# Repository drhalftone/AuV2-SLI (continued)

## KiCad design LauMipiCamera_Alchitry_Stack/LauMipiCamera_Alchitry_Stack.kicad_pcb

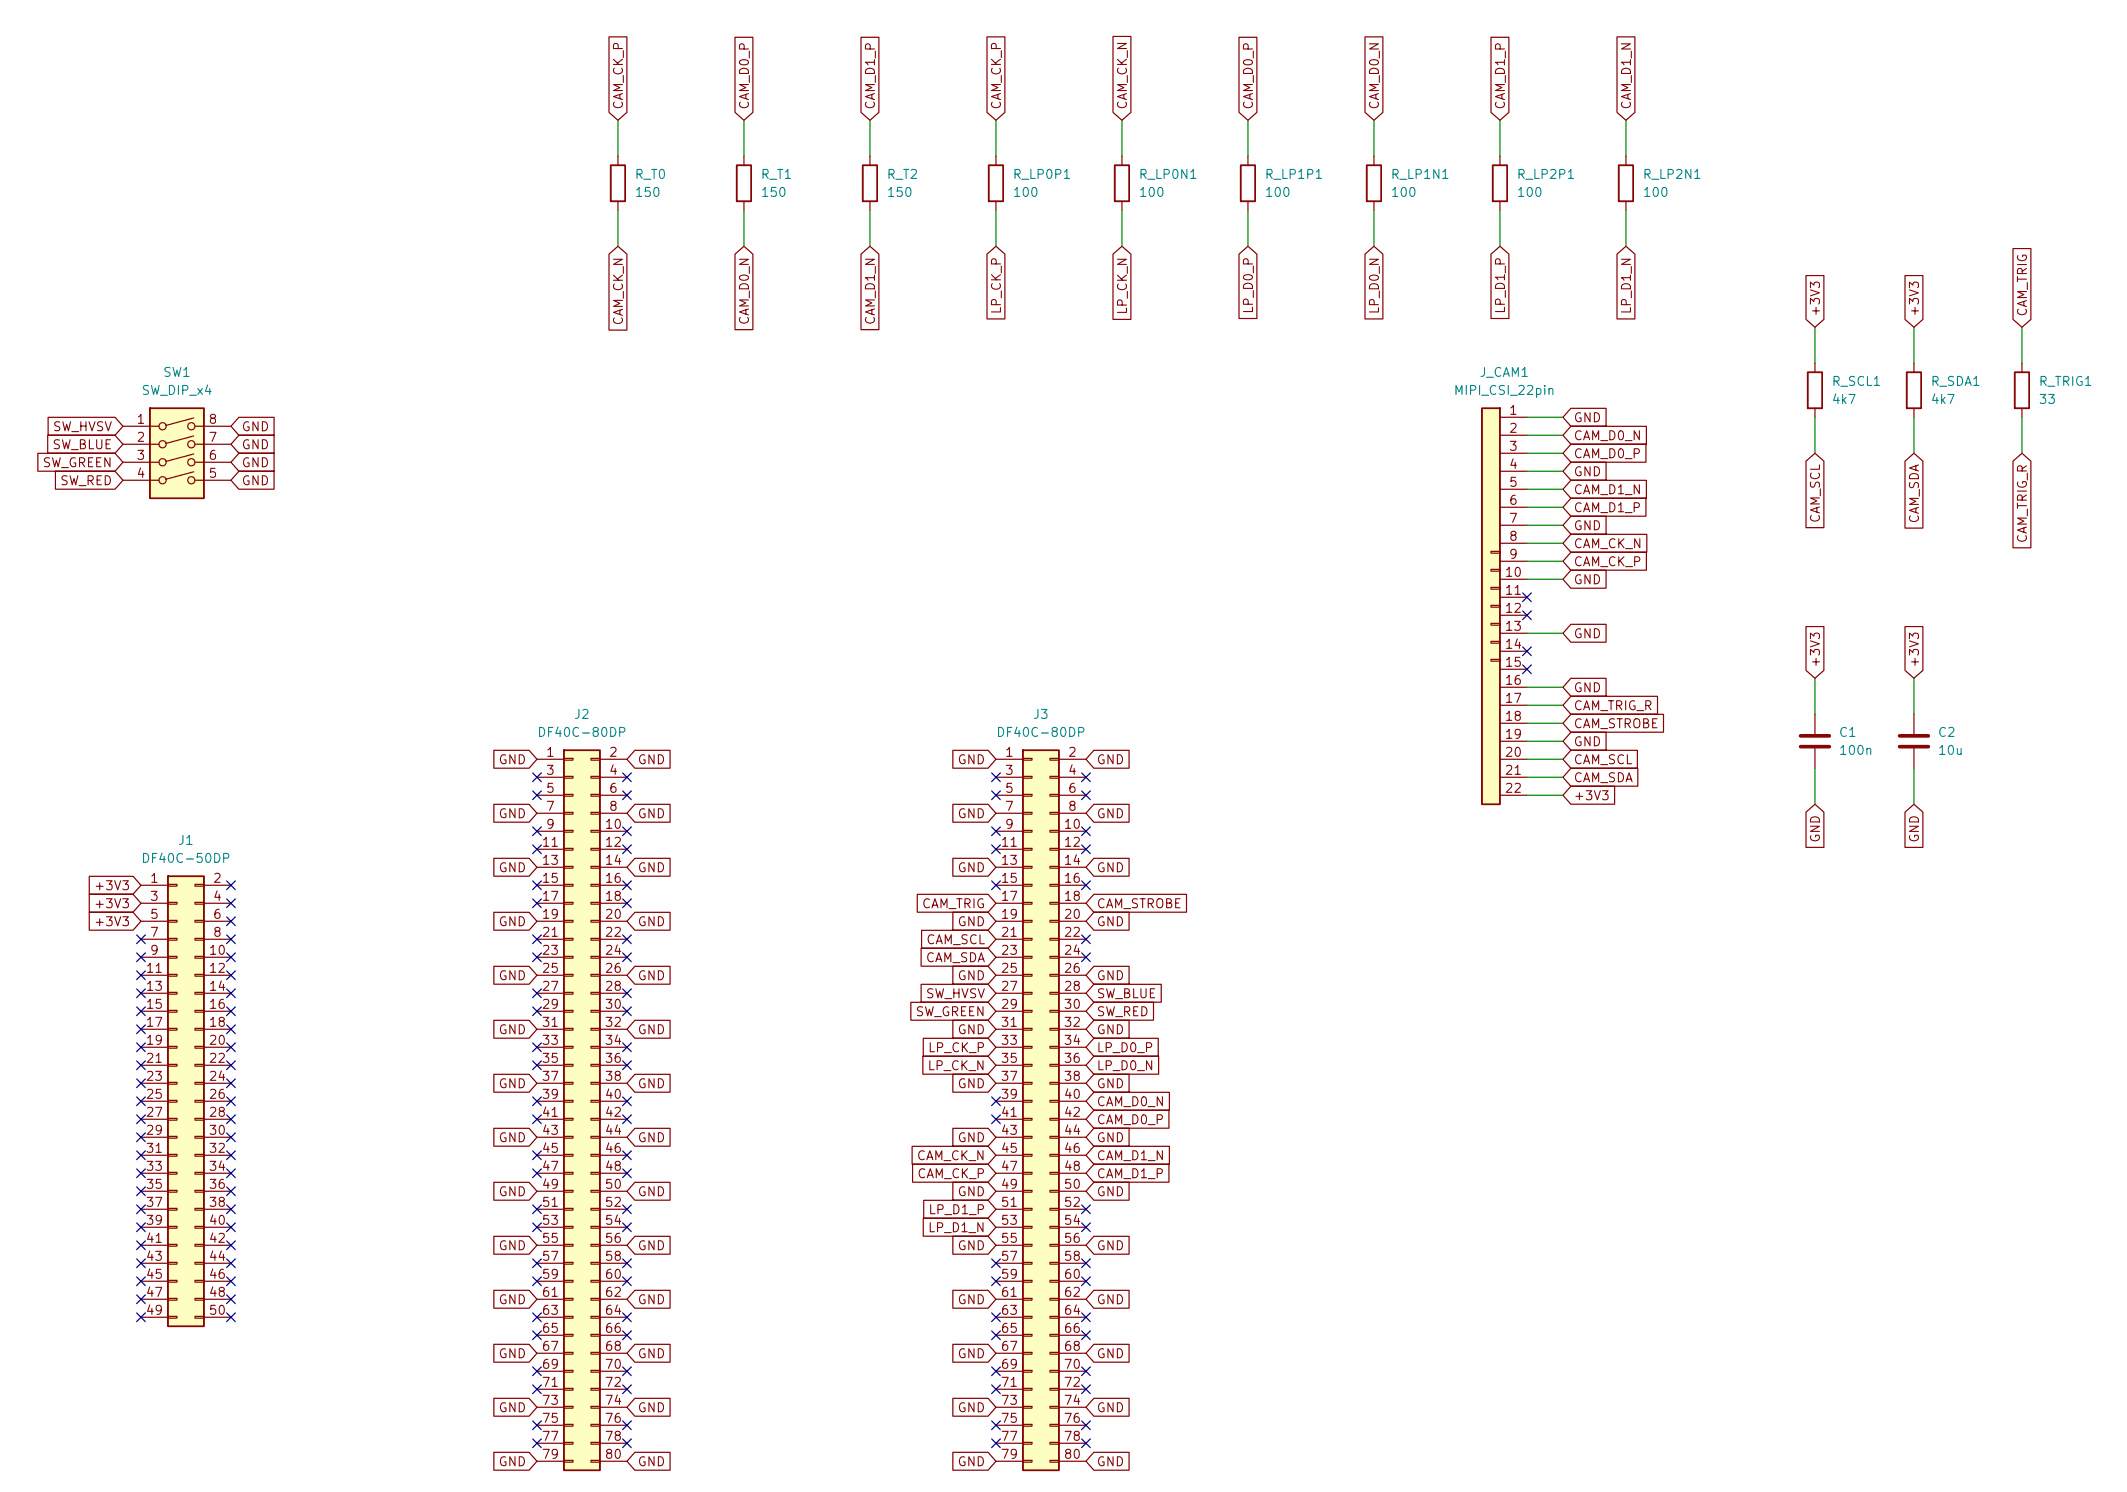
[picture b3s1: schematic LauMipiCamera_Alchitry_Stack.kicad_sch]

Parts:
C1: 100n; C_0805_2012Metric
C2: 10u; C_0805_2012Metric
J1: DF40C-50DP; Hirose_DF40C-50DP-0.4V_2x25-1MP_P0.4mm
J2, J3: DF40C-80DP; Hirose_DF40C-80DP-0.4V_2x40-1MP_P0.4mm
J_CAM1: MIPI_CSI_22pin; Hirose_FH12-22S-0.5SH_1x22-1MP_P0.50mm_Horizontal
R_LP0N1, R_LP0P1, R_LP1N1, R_LP1P1, R_LP2N1, R_LP2P1: 100; R_0402_1005Metric
R_SCL1: 4k7; R_0402_1005Metric
R_SDA1: 4k7; R_0402_1005Metric
R_T0, R_T1, R_T2: 150; R_0402_1005Metric
R_TRIG1: 33; R_0402_1005Metric
SW1: SW_DIP_x4; SW_DIP_SPSTx04_Slide_6.7x11.72mm_W8.61mm_P2.54mm_LowProfile

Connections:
+3V3: C1.1, C2.1, J1.1, J1.3, J1.5, J_CAM1.22, R_SCL1.1, R_SDA1.1
CAM_CK_N: J3.45, J_CAM1.8, R_LP0N1.1, R_T0.2
CAM_CK_P: J3.47, J_CAM1.9, R_LP0P1.1, R_T0.1
CAM_D0_N: J3.40, J_CAM1.2, R_LP1N1.1, R_T1.2
CAM_D0_P: J3.42, J_CAM1.3, R_LP1P1.1, R_T1.1
CAM_D1_N: J3.46, J_CAM1.5, R_LP2N1.1, R_T2.2
CAM_D1_P: J3.48, J_CAM1.6, R_LP2P1.1, R_T2.1
CAM_SCL: J3.21, J_CAM1.20, R_SCL1.2
CAM_SDA: J3.23, J_CAM1.21, R_SDA1.2
CAM_STROBE: J3.18, J_CAM1.18
CAM_TRIG: J3.17, R_TRIG1.1
CAM_TRIG_R: J_CAM1.17, R_TRIG1.2
GND: C1.2, C2.2, J2.1, J2.2, J2.7, J2.8, J2.13, J2.14, J2.19, J2.20, J2.25, J2.26, J2.31, J2.32, J2.37, J2.38, J2.43, J2.44, J2.49, J2.50, J2.55, J2.56, J2.61, J2.62, J2.67, J2.68, J2.73, J2.74, J2.79, J2.80, J3.1, J3.2, J3.7, J3.8, J3.13, J3.14, J3.19, J3.20, J3.25, J3.26, J3.31, J3.32, J3.37, J3.38, J3.43, J3.44, J3.49, J3.50, J3.55, J3.56, J3.61, J3.62, J3.67, J3.68, J3.73, J3.74, J3.79, J3.80, J_CAM1.1, J_CAM1.4, J_CAM1.7, J_CAM1.10, J_CAM1.13, J_CAM1.16, J_CAM1.19, SW1.5, SW1.6, SW1.7, SW1.8
LP_CK_N: J3.35, R_LP0N1.2
LP_CK_P: J3.33, R_LP0P1.2
LP_D0_N: J3.36, R_LP1N1.2
LP_D0_P: J3.34, R_LP1P1.2
LP_D1_N: J3.53, R_LP2N1.2
LP_D1_P: J3.51, R_LP2P1.2
SW_BLUE: J3.28, SW1.2
SW_GREEN: J3.29, SW1.3
SW_HVSV: J3.27, SW1.1
SW_RED: J3.30, SW1.4

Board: 4 copper layers, 19 parts (3 on the bottom side), 23 nets, no tracks yet.

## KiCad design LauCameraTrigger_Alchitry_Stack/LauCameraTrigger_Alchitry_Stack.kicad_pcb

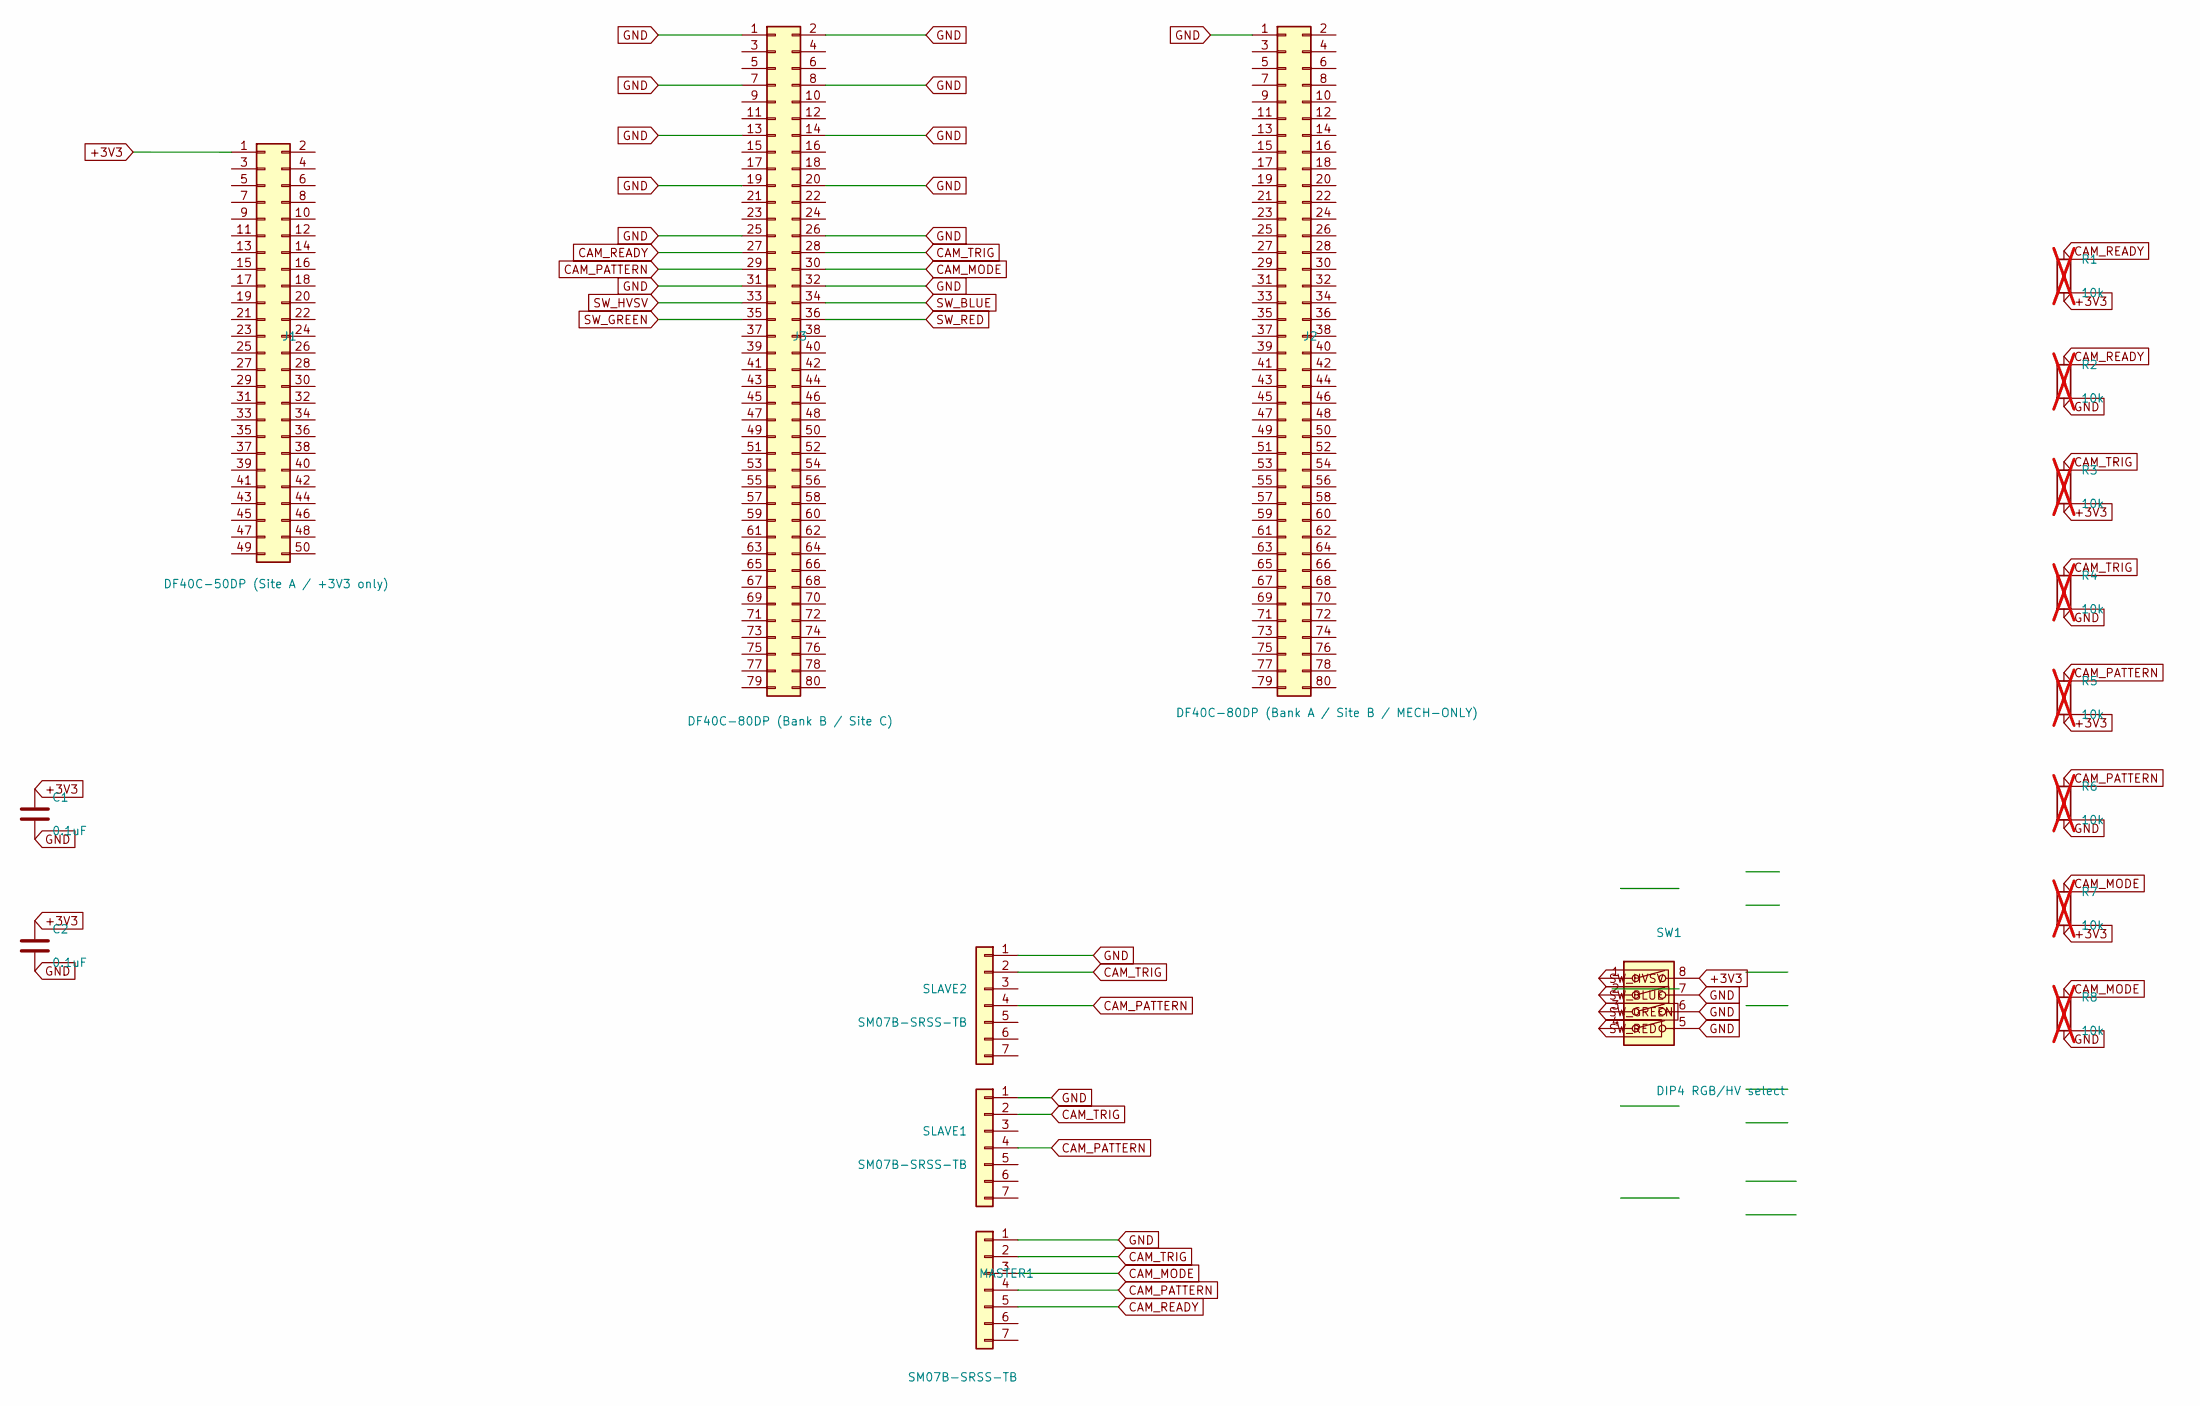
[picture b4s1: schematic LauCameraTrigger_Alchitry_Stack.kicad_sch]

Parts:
C1, C2: 0.1uF; C_0805_2012Metric
J1: DF40C-50DP (Site A / +3V3 only); Hirose_DF40C-50DP-0.4V_2x25-1MP_P0.4mm
J2: DF40C-80DP (Bank A / Site B / MECH-ONLY); Hirose_DF40C-80DP-0.4V_2x40-1MP_P0.4mm
J3: DF40C-80DP (Bank B / Site C); Hirose_DF40C-80DP-0.4V_2x40-1MP_P0.4mm
MASTER1: SM07B-SRSS-TB; JST_SH_SM07B-SRSS-TB_1x07-1MP_P1.00mm_Horizontal
R1, R2, R3, R4, R5, R6, R7, R8: 10k; R_1206_3216Metric; not fitted
SLAVE1, SLAVE2: SM07B-SRSS-TB; JST_SH_SM07B-SRSS-TB_1x07-1MP_P1.00mm_Horizontal
SW1: DIP4 RGB/HV select; SW_DIP_SPSTx04_Slide_6.7x11.72mm_W8.61mm_P2.54mm_LowProfile

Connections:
+3V3: C1.1, C2.1, J1.1 (Pin_1_1), R1.2, R3.2, R5.2, R7.2, SW1.8
CAM_MODE: J3.30, MASTER1.3, R7.1, R8.1
CAM_PATTERN: J3.29, MASTER1.4, R5.1, R6.1, SLAVE1.4, SLAVE2.4
CAM_READY: J3.27, MASTER1.5, R1.1, R2.1
CAM_TRIG: J3.28, MASTER1.2, R3.1, R4.1, SLAVE1.2, SLAVE2.2
GND: C1.2, C2.2, J2.1 (Pin_1_1), J3.1, J3.2, J3.7, J3.8, J3.13, J3.14, J3.19, J3.20, J3.25, J3.26, J3.31, J3.32, MASTER1.1, R2.2, R4.2, R6.2, R8.2, SLAVE1.1, SLAVE2.1, SW1.5, SW1.6, SW1.7
SW_BLUE: J3.34, SW1.2
SW_GREEN: J3.35, SW1.3
SW_HVSV: J3.33, SW1.1
SW_RED: J3.36, SW1.4

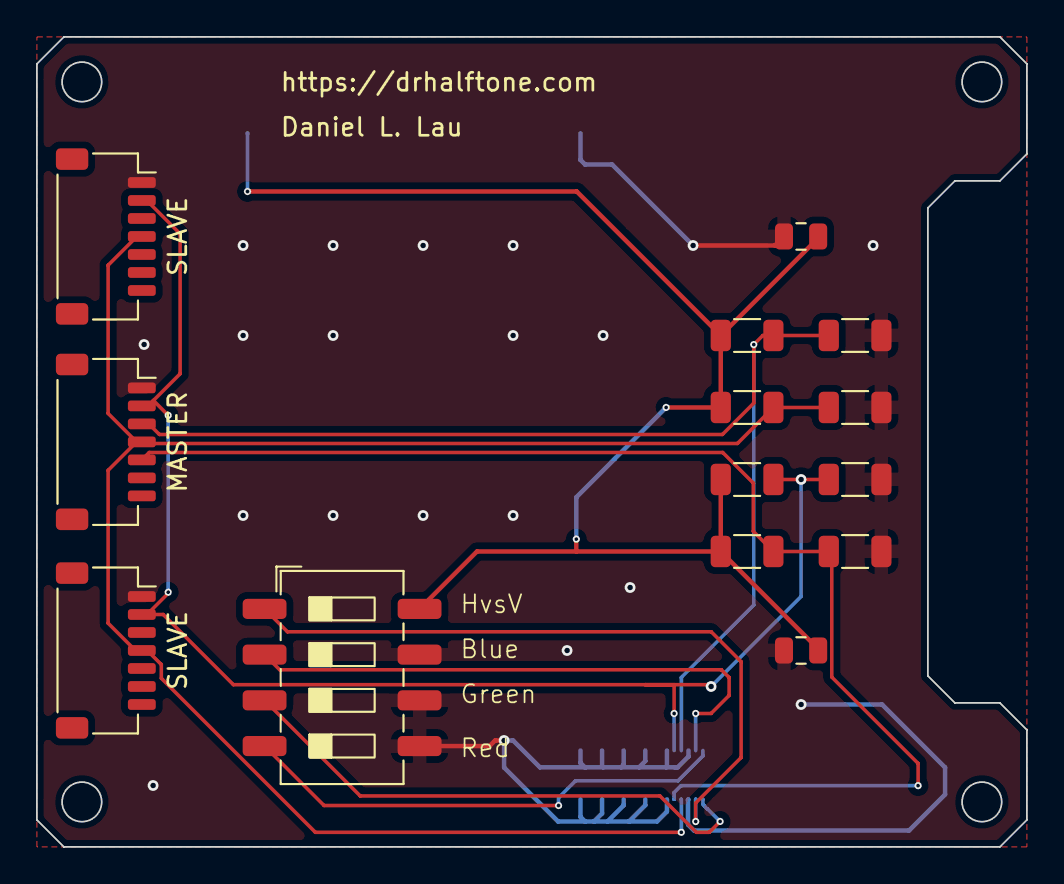
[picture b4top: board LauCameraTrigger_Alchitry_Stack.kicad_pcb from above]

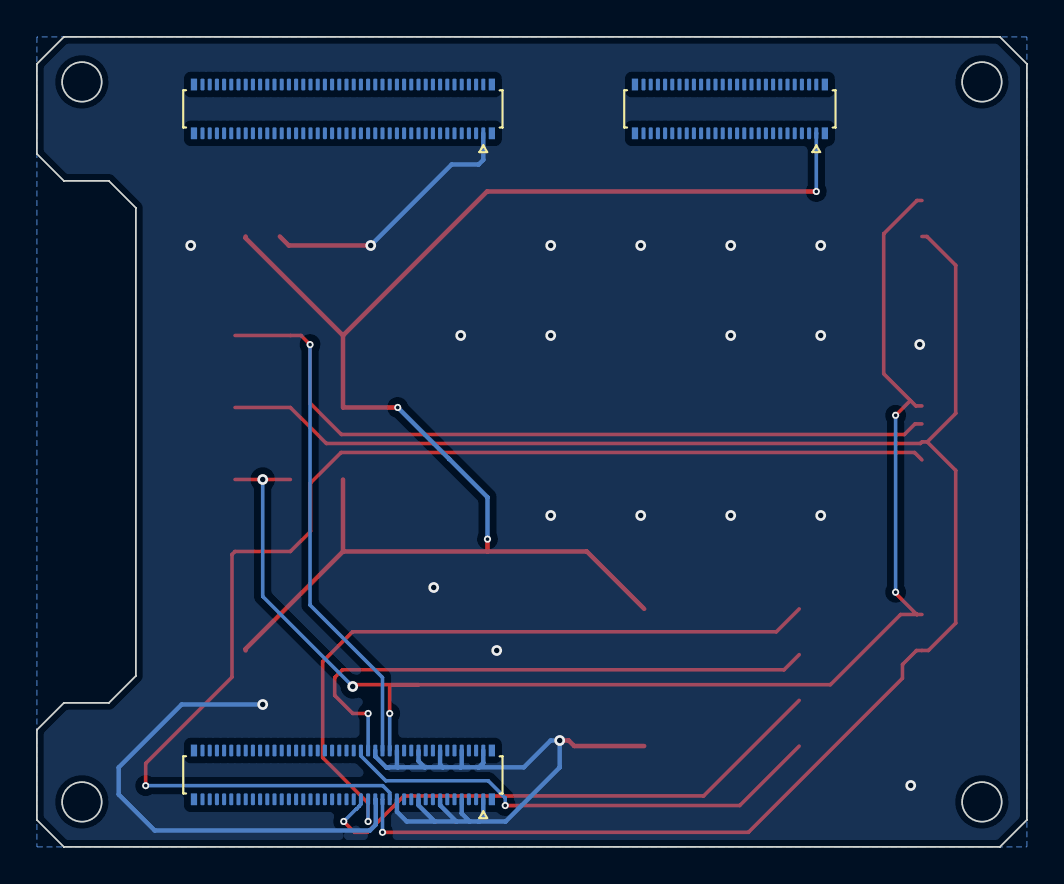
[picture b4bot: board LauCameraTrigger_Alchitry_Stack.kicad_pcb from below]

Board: 2 copper layers, 55.0 x 45.0 mm, 17 parts (3 on the bottom side), 10 nets.

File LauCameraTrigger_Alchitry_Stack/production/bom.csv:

Comment,Designator,Footprint,Qty,MPN,LCSC Part #
SM07B-SRSS-TB,"MASTER1,SLAVE1,SLAVE2",JST_SH_SM07B-SRSS-TB_1x07-1MP_P1.00mm_Horizontal,3,SM07B-SRSS-TB(LF)(SN),C160406
0.1uF,"C1,C2",C_0805_2012Metric,2,0.1uF 0805 X7R,C49678
DIP4 RGB/HV select -- DNP for PCBA; hand-solder (Wurth 418121160804),SW1,SW_DIP_SPSTx04_Slide_6.7x11.72mm_W8.61mm_P2.54mm_LowProfile,1,418121160804,
DF40C-80DP (Bank A / Site B / MECH-ONLY),J2,Hirose_DF40C-80DP-0.4V_2x40-1MP_P0.4mm,1,DF40C-80DP-0.4V(51),C294544
DF40C-80DP (Bank B / Site C),J3,Hirose_DF40C-80DP-0.4V_2x40-1MP_P0.4mm,1,DF40C-80DP-0.4V(51),C294544
DF40C-50DP (Site A / +3V3 only),J1,Hirose_DF40C-50DP-0.4V_2x25-1MP_P0.4mm,1,DF40C-50DP-0.4V(51),C424645

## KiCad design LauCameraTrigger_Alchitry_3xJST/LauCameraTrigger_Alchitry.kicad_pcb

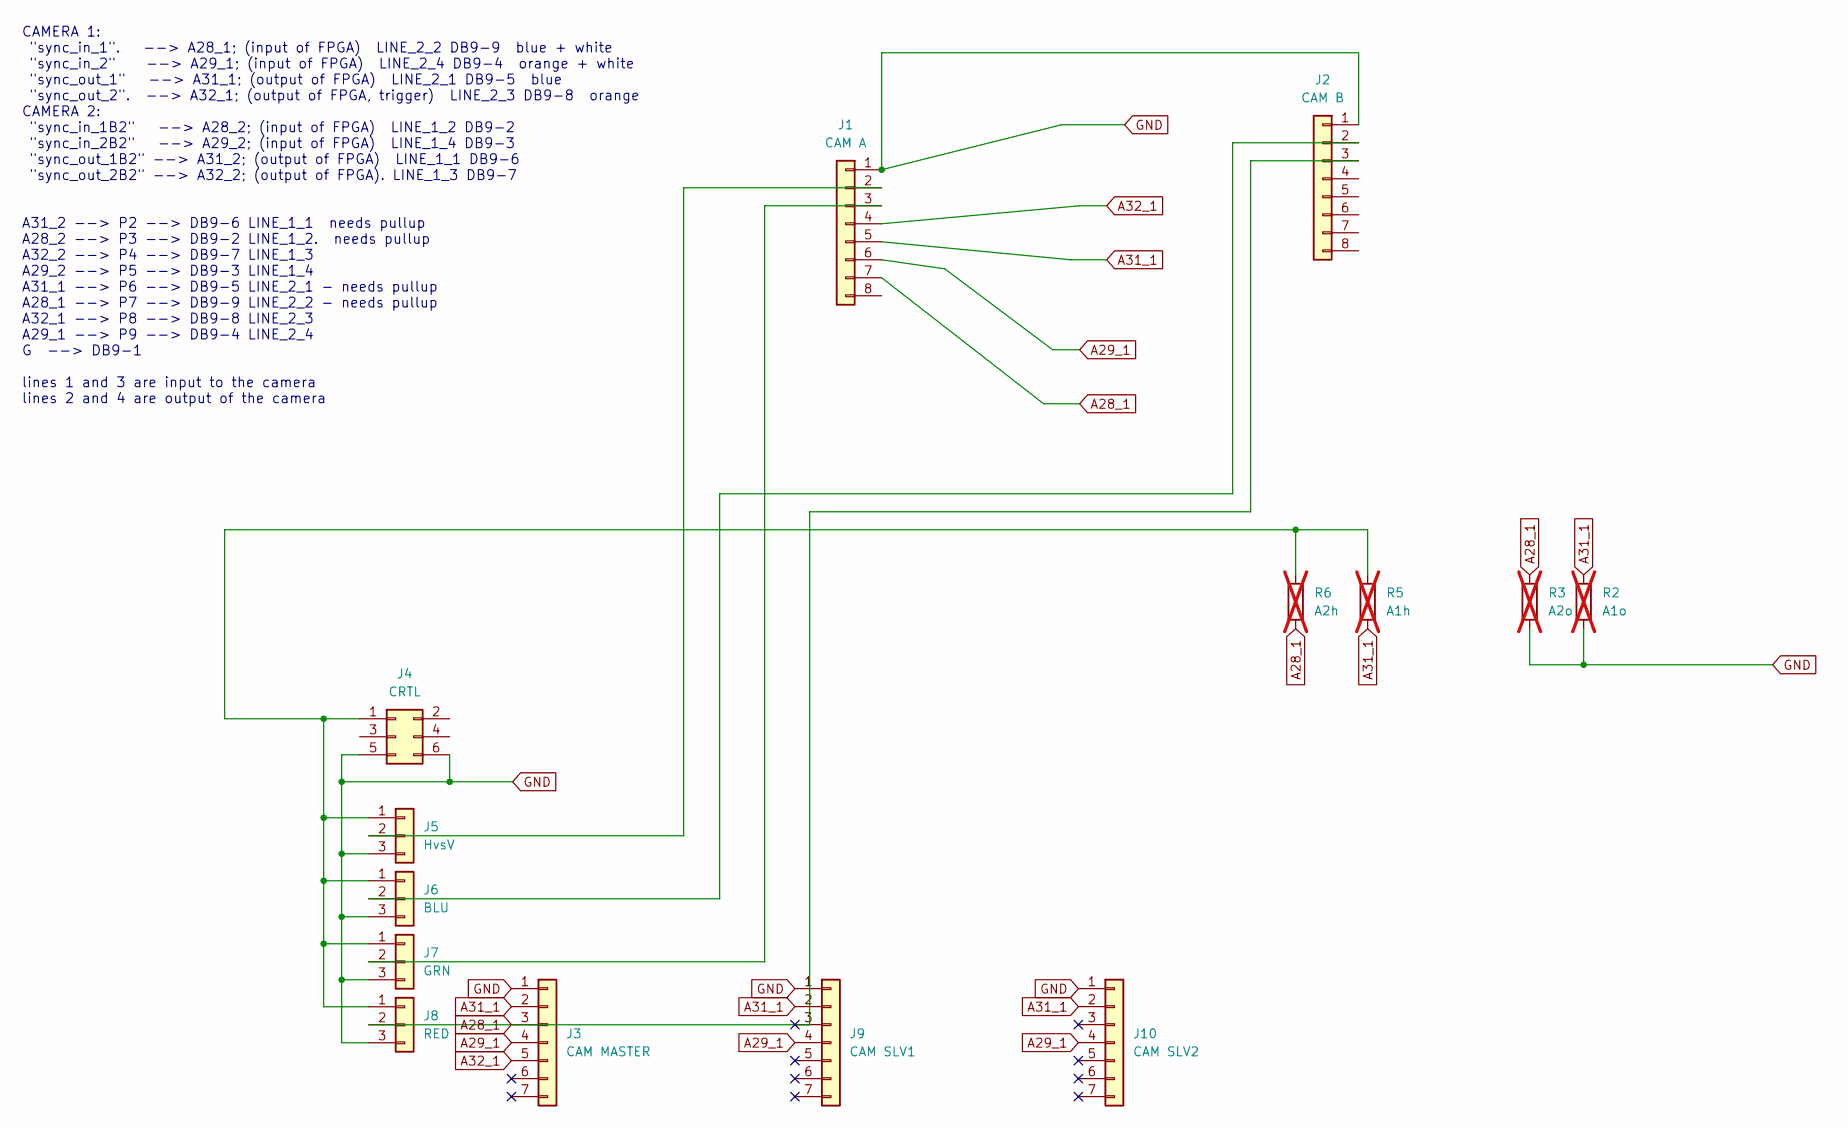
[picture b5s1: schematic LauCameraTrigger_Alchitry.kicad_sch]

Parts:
J1: CAM A; PinHeader_1x08_P2.54mm_Vertical
J2: CAM B; PinHeader_1x08_P2.54mm_Vertical
J3: CAM MASTER; JST_SH_SM07B-SRSS-TB_1x07-1MP_P1.00mm_Horizontal; MPN SM07B-SRSS-TB(LF)(SN)
J4: CRTL; PinHeader_2x03_P2.54mm_Vertical
J5: HvsV; PinHeader_1x03_P2.54mm_Vertical
J6: BLU; PinHeader_1x03_P2.54mm_Vertical
J7: GRN; PinHeader_1x03_P2.54mm_Vertical
J8: RED; PinHeader_1x03_P2.54mm_Vertical
J9: CAM SLV1; JST_SH_SM07B-SRSS-TB_1x07-1MP_P1.00mm_Horizontal; MPN SM07B-SRSS-TB(LF)(SN)
J10: CAM SLV2; JST_SH_SM07B-SRSS-TB_1x07-1MP_P1.00mm_Horizontal; MPN SM07B-SRSS-TB(LF)(SN)
R2: A1o; R_Axial_DIN0207_L6.3mm_D2.5mm_P10.16mm_Horizontal; not fitted
R3: A2o; R_Axial_DIN0207_L6.3mm_D2.5mm_P10.16mm_Horizontal; not fitted
R5: A1h; R_Axial_DIN0207_L6.3mm_D2.5mm_P10.16mm_Horizontal; not fitted
R6: A2h; R_Axial_DIN0207_L6.3mm_D2.5mm_P10.16mm_Horizontal; not fitted

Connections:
A28_1: J1.7, J3.3, R3.1, R6.2
A29_1: J1.6, J3.4, J9.4, J10.4
A31_1: J1.5, J3.2, J9.2, J10.2, R2.1, R5.2
A32_1: J1.4, J3.5
GND: J1.1, J2.1, J3.1, J4.5, J4.6, J5.3, J6.3, J7.3, J8.3, J9.1, J10.1, R2.2, R3.2
unnamed: J1.2, J5.2
unnamed: J1.3, J7.2
unnamed: J2.2, J6.2
unnamed: J2.3, J8.2
unnamed: J4.1, J5.1, J6.1, J7.1, J8.1, R5.1, R6.1

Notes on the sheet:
CAMERA 1: "sync_in_1". --> A28_1; (input of FPGA) LINE_2_2 DB9-9 blue + white "sync_in_2" --> A29_1; (input of FPGA) LINE_2_4 DB9-4 orange + white "sync_out_1" --> A31_1; (output of FPGA) LINE_2_1 DB9-5 blue "sync_out_2". --> A32_1; (output of FPGA, trigger) LINE_2_3 DB9-8 orange CAMERA 2: "sync_in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

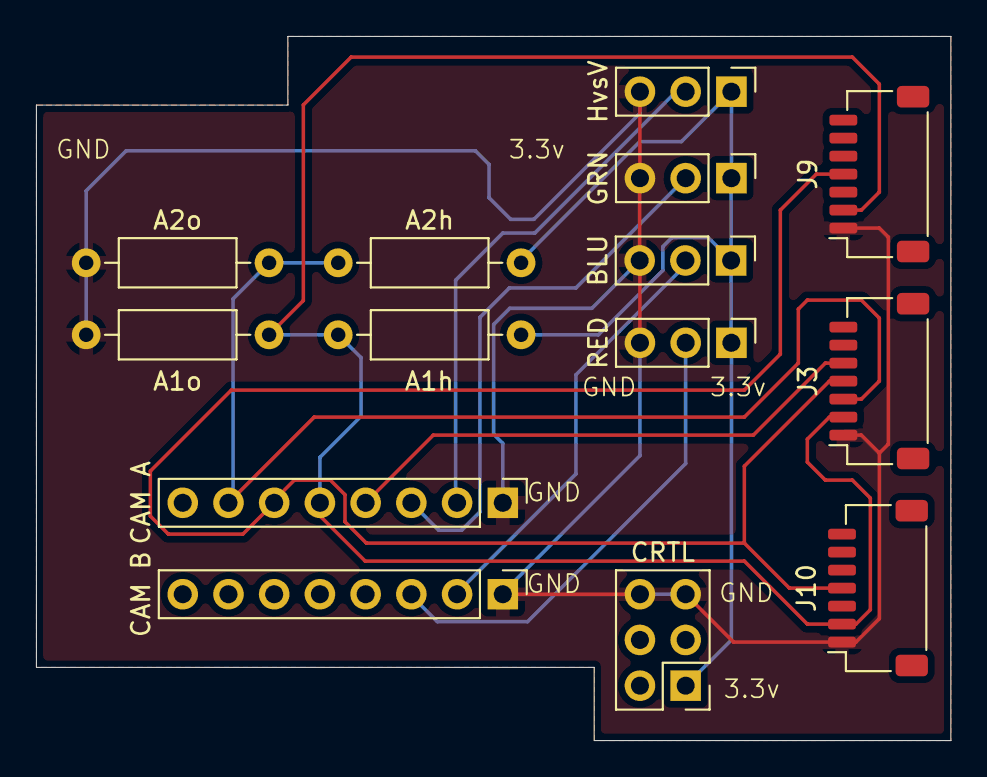
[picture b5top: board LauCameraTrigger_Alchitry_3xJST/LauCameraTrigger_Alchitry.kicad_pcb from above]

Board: 2 copper layers, 50.8 x 39.1 mm, 14 parts (0 on the bottom side), 10 nets.

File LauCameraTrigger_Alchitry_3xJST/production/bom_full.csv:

"Comment","Designator","Footprint","Qty","MPN","Manufacturer"
"CAM A,CAM B","J1,J2","Connector_PinHeader_2.54mm:PinHeader_1x08_P2.54mm_Vertical","2","",""
"CAM MASTER,CAM SLV1,CAM SLV2","J3,J9,J10","Connector_JST:JST_SH_SM07B-SRSS-TB_1x07-1MP_P1.00mm_Horizontal","3","SM07B-SRSS-TB(LF)(SN)","JST"
"CRTL","J4","Connector_PinHeader_2.54mm:PinHeader_2x03_P2.54mm_Vertical","1","",""
"BLU,GRN,HvsV,RED","J5-J8","Connector_PinHeader_2.54mm:PinHeader_1x03_P2.54mm_Vertical","4","",""

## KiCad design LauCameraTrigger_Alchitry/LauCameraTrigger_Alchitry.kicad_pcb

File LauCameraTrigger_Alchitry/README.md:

# LauCameraTrigger — Alchitry camera-trigger breakout PCB

A small KiCad breakout board that connects the **Alchitry Au V2 + Br V2** GPIO to the
structured-light **cameras**, carrying the 4-line trigger/handshake protocol
(trigger out, first-frame/pattern out, camera-ready in, mode in) over a **DB-9** camera port.
It is the hardware companion to the [AuV2-SLI](../README.md) FPGA design.

This folder contains the **minimum KiCad source** needed to fabricate and assemble the board,
plus the **camera-wiring documents** for connecting Basler and Allied Vision USB-3 cameras.

---

## Files in this folder

### KiCad project (order + assemble from these three)
| File | What it is |
|---|---|
| `LauCameraTrigger_Alchitry.kicad_pro` | KiCad 7 project file. |
| `LauCameraTrigger_Alchitry.kicad_sch` | Schematic — the BOM and assembly reference. |
| `LauCameraTrigger_Alchitry.kicad_pcb` | Board layout. Footprints/geometry are embedded, so this file is self-contained — plot Gerbers + drill from it, or upload it directly to a fab (e.g. JLCPCB/PCBWay). |

The board is a passive interconnect: **1× DB-9 (DE9) camera port**, **2× 1×08 + 4× 1×03 + 1× 2×03
0.1″ pin headers** to the Br V2 GPIO, and **8 axial resistors** (line series/pull resistors). All
footprints are standard KiCad libraries; no custom library is required.

### Camera-wiring documents
| File | Covers |
|---|---|
| `Basler_ACE_USB_GPIO_Wiring_Guide.md` | **Basler ACE USB 3.0** (Hirose 6-pin / Opto-GP-I/O Y-cable) → DB-9. Pinout, wire colors, opto-isolated vs. TTL lines, pull-up/level-shift notes, Pylon SDK config. |
| `Alvium_1800_GPIO_Wiring_Guide.md` | **Allied Vision Alvium 1800 USB** (JST 7-pin) → DB-9. Pinout, wire colors, 3.3 V push-pull GPIO (no pull-ups needed), Vimba SDK config. |
| `Alvium_Three_Camera_DB9_Harness.md` | External harness combining **three Alvium cameras into one DB-9** (1 master + 2 slaves) so the slaves share the broadcast trigger without bus contention. |
| `Alvium_Three_Camera_Onboard_JST_PCB.md` | A **variant of *this* board** that replaces the DB-9 with **three on-board JST-7 connectors** — cameras plug in with 1:1 JST cables (the "JST-to-PCB" build). Lists the exact schematic edits and the `Connector_JST` footprint. |
| `Vimba_FPGA_LCG_Timing_Guide.md` | Camera **timing & GPIO handshake** settings (trigger delay, exposure, FrameTriggerWait) for FPGA-triggered SLI capture. |

---

## Ordering the PCB

1. Open `LauCameraTrigger_Alchitry.kicad_pcb` in KiCad 7+.
2. **File → Plot** → Gerbers, and **Fabrication Outputs → Drill Files** — or upload the
   `.kicad_pcb` straight to a fab that accepts it.
3. Run **DRC** first if you've edited anything.

## Assembling

Use `LauCameraTrigger_Alchitry.kicad_sch` to generate the BOM (DB-9 receptacle, the 0.1″ headers,
and the 8 resistors). Then build the **camera cable** for your camera from the matching wiring guide
above (Basler or Alvium), which maps each camera line to the DB-9 pins the board expects.

---

## Notes before you build

- **DB-9 vs. JST.** This board uses a **DB-9** camera port; cameras attach via a JST→DB-9 cable
  (per the wiring guides). If you'd rather the cameras plug **directly** into the board with JST
  cables, build the on-board JST-7 variant in `Alvium_Three_Camera_Onboard_JST_PCB.md`.
- **Header pin labels.** The schematic's FPGA-side nets use the DB-9 harness convention
  (`A28/A29/A31/A32`). Confirm these line up with the FPGA constraints
  (`../constrs_1/imports/RTL/Au2.xdc`, which uses `A17/A23/A29/A35` for camera 1) before relying on
  the trigger lines — the two numbering schemes differ.
- **Camera 2 is outputs-only in the current AuV2 bitstream.** The DB-9 exposes a second camera
  channel, but `C2_in` (camera-ready / mode) is unbound in `Au2.xdc` — camera 2 receives triggers
  but its ready handshake isn't read. See the wiring guides and the main README for details.
- **Basler needs extra parts on the Br V2.** Basler Line 2 is open-collector (needs a pull-up) and
  Line 1 is opto-isolated (needs 5–24 V drive). The stock Br V2 provides neither, so add them
  externally for a Basler. The Alvium (3.3 V push-pull) works directly.

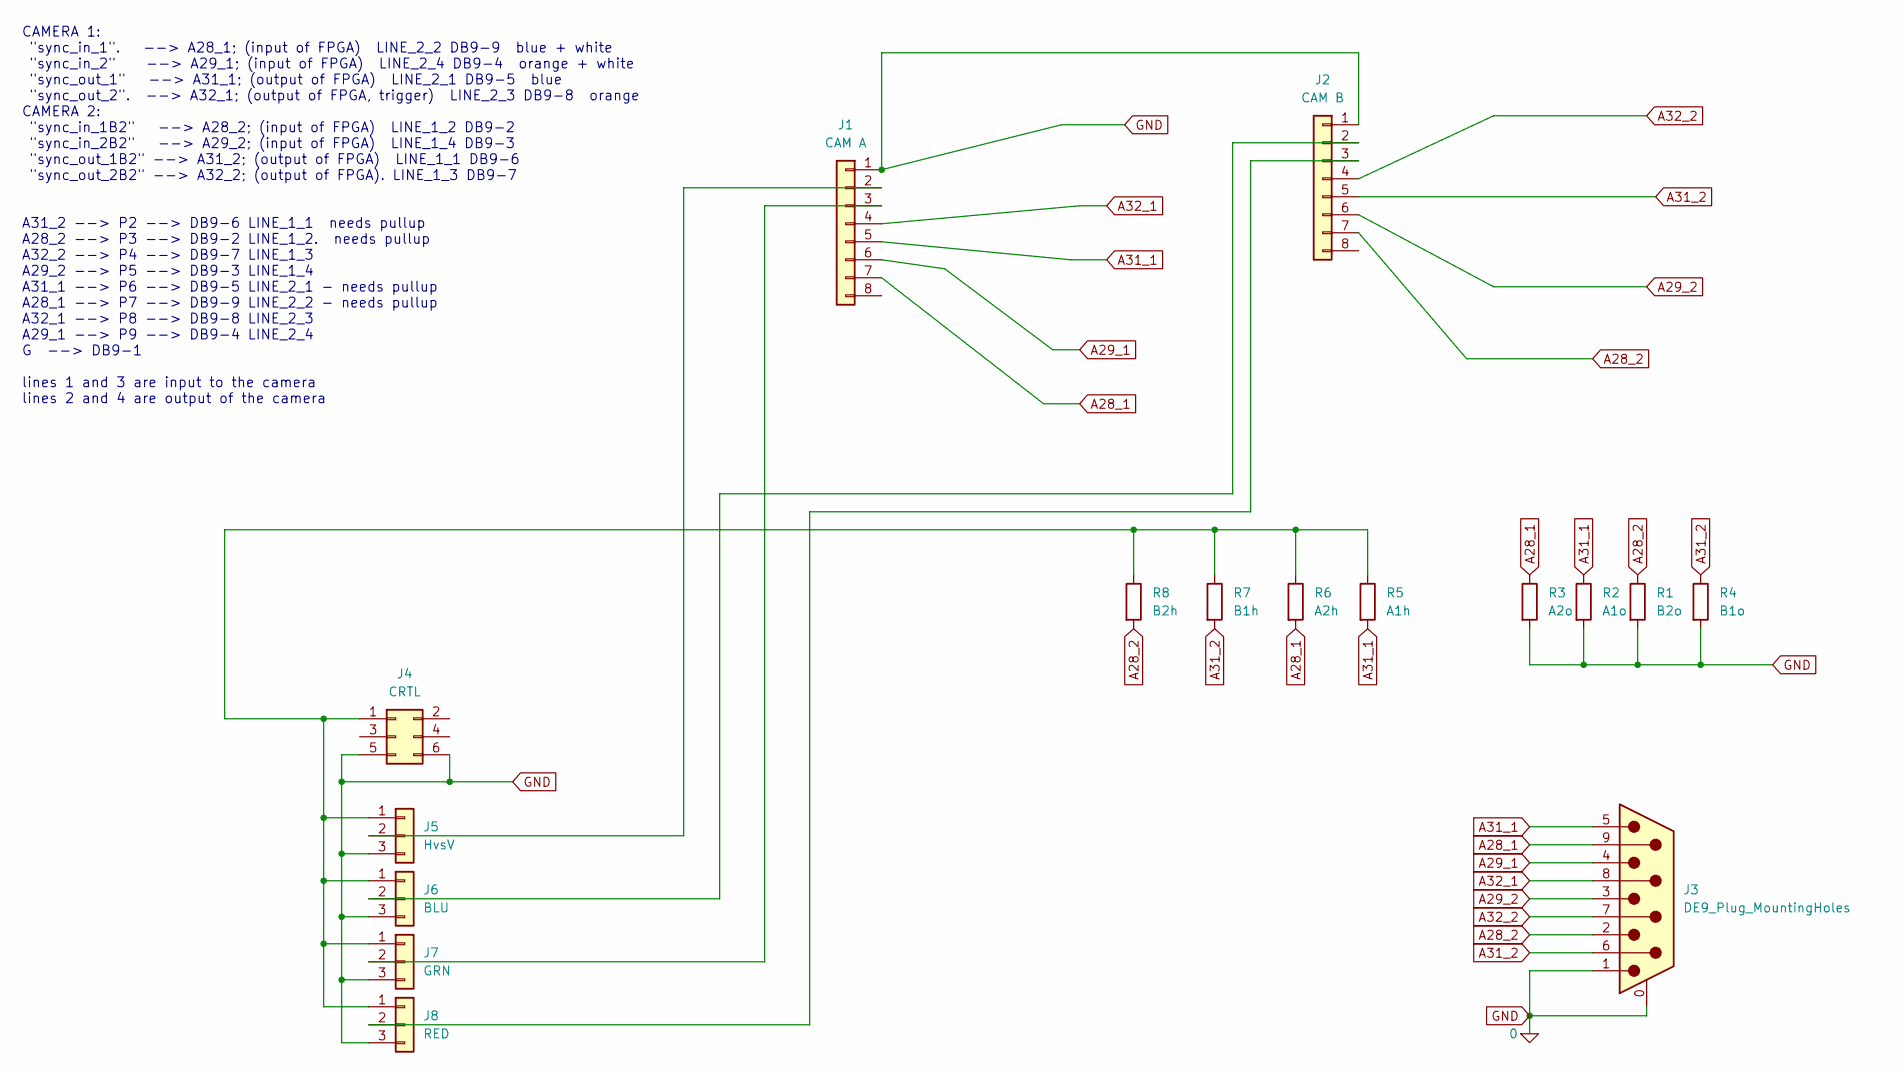
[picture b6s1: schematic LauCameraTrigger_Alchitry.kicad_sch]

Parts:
J1: CAM A; PinHeader_1x08_P2.54mm_Vertical
J2: CAM B; PinHeader_1x08_P2.54mm_Vertical
J3: DE9_Plug_MountingHoles; DSUB-9_Pins_Horizontal_P2.77x2.84mm_EdgePinOffset4.94mm_Hou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
J4: CRTL; PinHeader_2x03_P2.54mm_Vertical
J5: HvsV; PinHeader_1x03_P2.54mm_Vertical
J6: BLU; PinHeader_1x03_P2.54mm_Vertical
J7: GRN; PinHeader_1x03_P2.54mm_Vertical
J8: RED; PinHeader_1x03_P2.54mm_Vertical
R1: B2o; R_Axial_DIN0207_L6.3mm_D2.5mm_P10.16mm_Horizontal
R2: A1o; R_Axial_DIN0207_L6.3mm_D2.5mm_P10.16mm_Horizontal
R3: A2o; R_Axial_DIN0207_L6.3mm_D2.5mm_P10.16mm_Horizontal
R4: B1o; R_Axial_DIN0207_L6.3mm_D2.5mm_P10.16mm_Horizontal
R5: A1h; R_Axial_DIN0207_L6.3mm_D2.5mm_P10.16mm_Horizontal
R6: A2h; R_Axial_DIN0207_L6.3mm_D2.5mm_P10.16mm_Horizontal
R7: B1h; R_Axial_DIN0207_L6.3mm_D2.5mm_P10.16mm_Horizontal
R8: B2h; R_Axial_DIN0207_L6.3mm_D2.5mm_P10.16mm_Horizontal

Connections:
A28_1: J1.7, J3.9, R3.1, R6.2
A28_2: J2.7, J3.2, R1.1, R8.2
A29_1: J1.6, J3.4
A29_2: J2.6, J3.3
A31_1: J1.5, J3.5, R2.1, R5.2
A31_2: J2.5, J3.6, R4.1, R7.2
A32_1: J1.4, J3.8
A32_2: J2.4, J3.7
GND: J1.1, J2.1, J3.0 (PAD), J3.1, J4.5, J4.6, J5.3, J6.3, J7.3, J8.3, R1.2, R2.2, R3.2, R4.2
unnamed: J1.2, J5.2
unnamed: J1.3, J7.2
unnamed: J2.2, J6.2
unnamed: J2.3, J8.2
unnamed: J4.1, J5.1, J6.1, J7.1, J8.1, R5.1, R6.1, R7.1, R8.1

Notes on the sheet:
CAMERA 1: "sync_in_1". --> A28_1; (input of FPGA) LINE_2_2 DB9-9 blue + white "sync_in_2" --> A29_1; (input of FPGA) LINE_2_4 DB9-4 orange + white "sync_out_1" --> A31_1; (output of FPGA) LINE_2_1 DB9-5 blue "sync_out_2". --> A32_1; (output of FPGA, trigger) LINE_2_3 DB9-8 orange CAMERA 2: "sync_in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

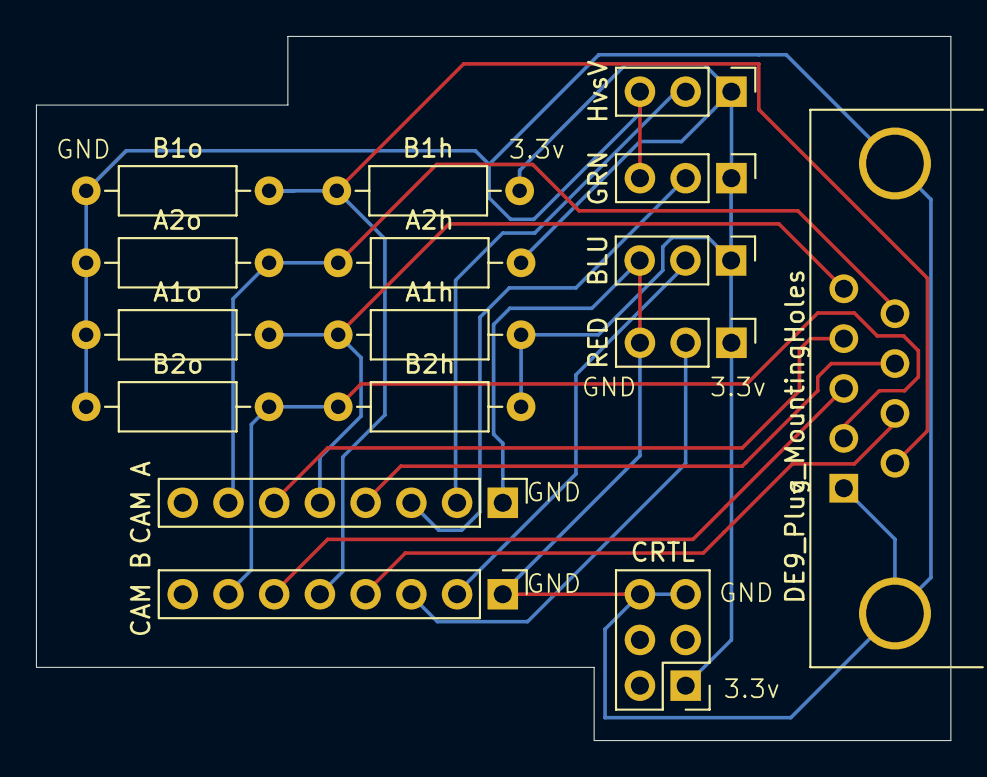
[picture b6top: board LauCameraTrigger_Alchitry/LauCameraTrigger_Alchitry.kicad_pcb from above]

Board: 2 copper layers, 50.8 x 39.1 mm, 16 parts (0 on the bottom side), 14 nets.

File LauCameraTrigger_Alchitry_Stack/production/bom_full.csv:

Comment,Designator,Footprint,Qty,MPN
SM07B-SRSS-TB,"MASTER1,SLAVE1,SLAVE2",JST_SH_SM07B-SRSS-TB_1x07-1MP_P1.00mm_Horizontal,3,SM07B-SRSS-TB(LF)(SN)
10k,"R1,R2,R3,R4,R5,R6,R7,R8",R_1206_3216Metric,8,
0.1uF,"C1,C2",C_0805_2012Metric,2,
DIP4 RGB/HV select,SW1,SW_DIP_SPSTx04_Slide_6.7x11.72mm_W8.61mm_P2.54mm_LowProfile,1,
DF40C-80DP (Bank A / Site B / MECH-ONLY),J2,Hirose_DF40C-80DP-0.4V_2x40-1MP_P0.4mm,1,DF40C-80DP-0.4V(51)
DF40C-80DP (Bank B / Site C),J3,Hirose_DF40C-80DP-0.4V_2x40-1MP_P0.4mm,1,DF40C-80DP-0.4V(51)
DF40C-50DP (Site A / +3V3 only),J1,Hirose_DF40C-50DP-0.4V_2x25-1MP_P0.4mm,1,DF40C-50DP-0.4V(51)
